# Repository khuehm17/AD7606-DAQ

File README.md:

# AD7606-DAQ

## Hardware
- STM32F103
- ADC Module: AD7606

## Firmware
- C/C++
- STM HAL Driver

### References
- Official AD7606 driver from Analog: https://github.com/analogdevicesinc/no-OS/tree/master/drivers/adc/ad7606
- MrWangShai project: https://github.com/MrWangShuai/stm32-AD7606
- Official AD7606 datasheet: https://www.analog.com/media/en/technical-documentation/data-sheets/ad7606_7606-6_7606-4.pdf
- Official STM32F103 manual: https://www.st.com/resource/en/reference_manual/cd00171190-stm32f101xx-stm32f102xx-stm32f103xx-stm32f105xx-and-stm32f107xx-advanced-arm-based-32-bit-mcus-stmicroelectronics.pdf

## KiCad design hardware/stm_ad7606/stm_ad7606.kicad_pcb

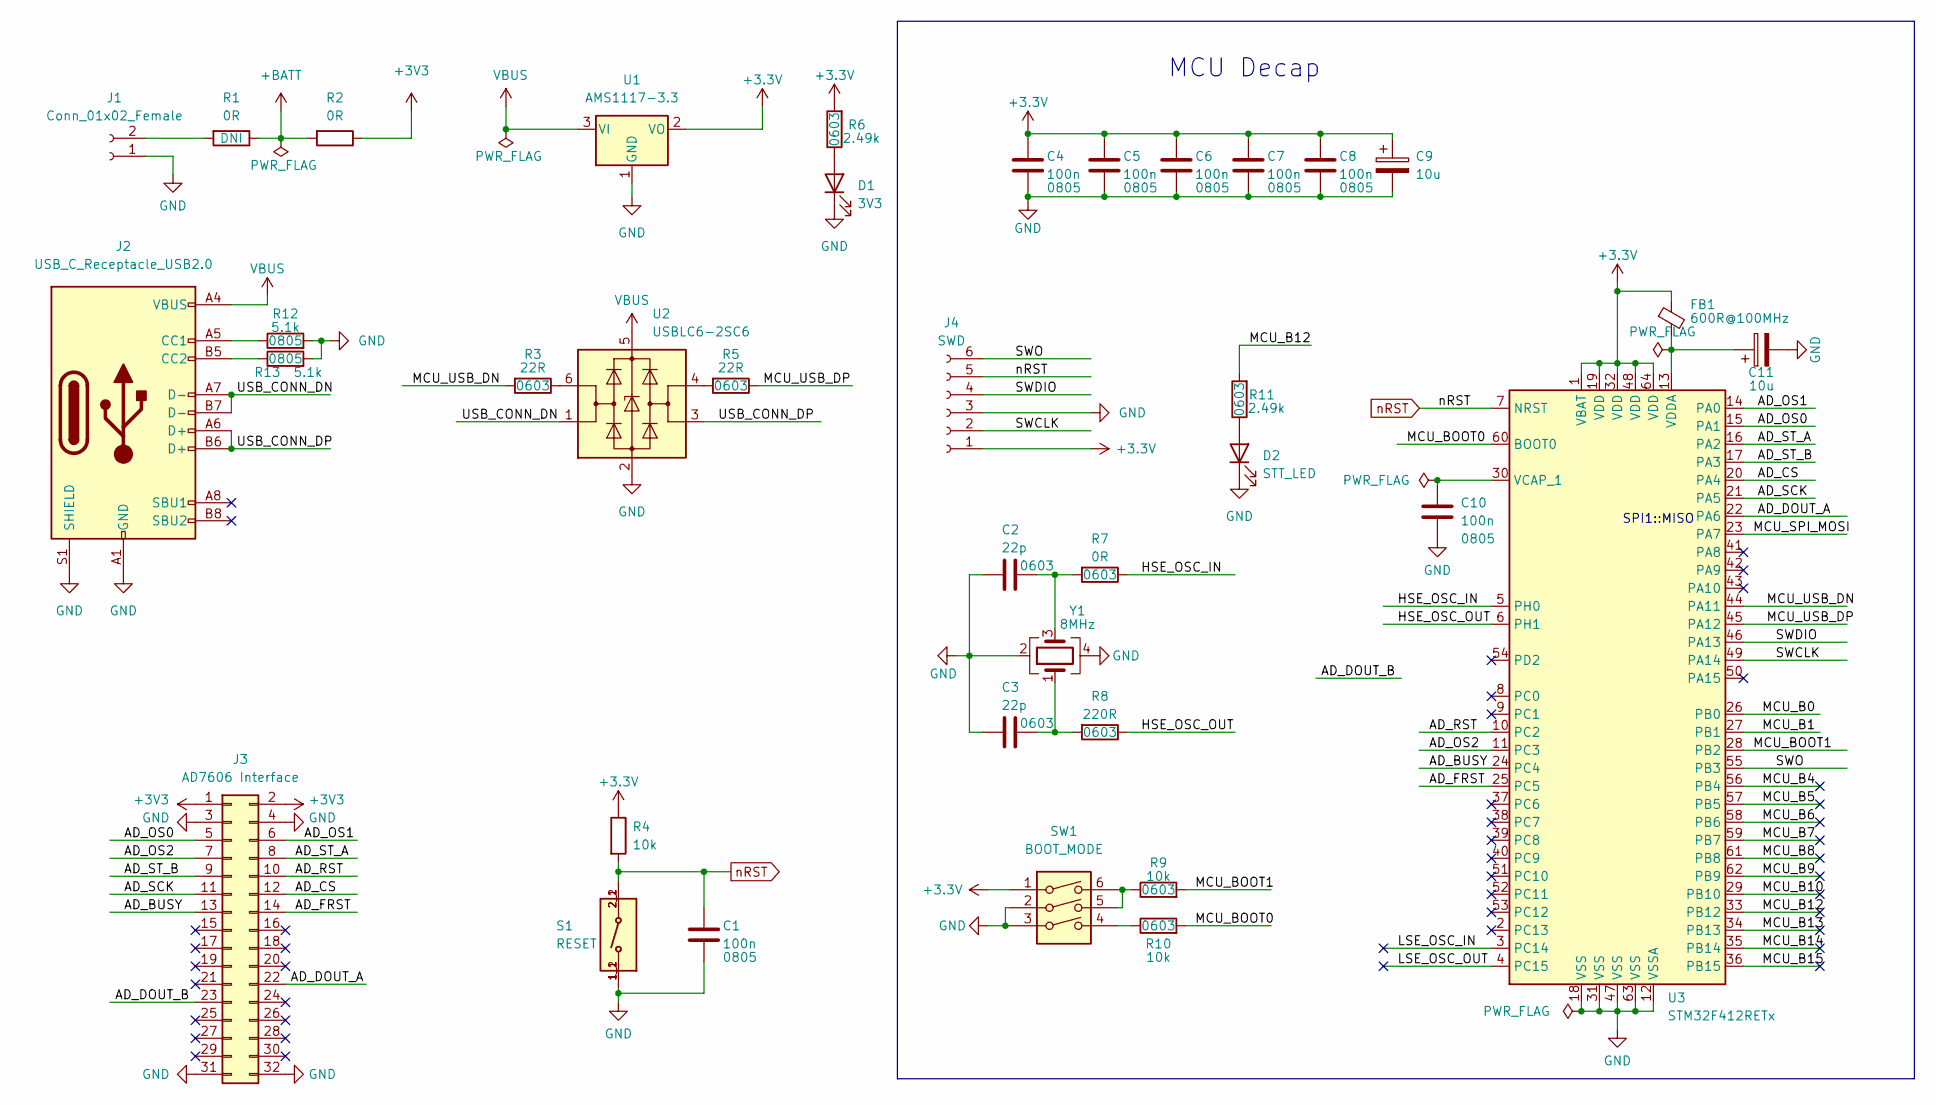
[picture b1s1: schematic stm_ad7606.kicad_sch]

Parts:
C1, C4, C5, C6, C7, C8, C10: 100n; C_0805_2012Metric
C2, C3: 22p; C_0603_1608Metric
C9, C11: 10u; CP_EIA-3216-10_Kemet-I
D1: 3V3; LED_0805_2012Metric
D2: STT_LED; LED_0805_2012Metric
FB1: 600R@100MHz; L_0805_2012Metric
J1: Conn_01x02_Female; JST_PH_B2B-PH-K_1x02_P2.00mm_Vertical
J2: USB_C_Receptacle_USB2.0; USB_C_Receptacle_HRO_TYPE-C-31-M-12
J3: AD7606 Interface; PinHeader_2x16_P2.54mm_Vertical
J4: SWD; PinHeader_1x06_P2.54mm_Vertical
R1, R2, R7: 0R; R_0603_1608Metric
R3, R5: 22R; R_0603_1608Metric
R4: 10k; R_0805_2012Metric
R6, R11: 2.49k; R_0603_1608Metric
R8: 220R; R_0603_1608Metric
R9, R10: 10k; R_0603_1608Metric
R12, R13: 5.1k; R_0805_2012Metric
S1: RESET; SW_KMR621NGLFS; PARTREV N/A
SW1: BOOT_MODE; SW_DIP_SPSTx03_Slide_KingTek_DSHP03TS_W7.62mm_P1.27mm
U1: AMS1117-3.3; SOT-223-3_TabPin2
U2: USBLC6-2SC6; SOT-23-6
U3: STM32F412RETx; LQFP-64_10x10mm_P0.5mm
Y1: 8MHz; Crystal_SMD_5032-4Pin_5.0x3.2mm

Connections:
+BATT: R1.1, R2.2
/AD_BUSY: J3.13, U3.24 (PC4)
/AD_CS: J3.12, U3.20 (PA4)
/AD_DOUT_A: J3.22, U3.22 (PA6)
/AD_DOUT_B: J3.23
/AD_FRST: J3.14, U3.25 (PC5)
/AD_OS0: J3.5, U3.15 (PA1)
/AD_OS1: J3.6, U3.14 (PA0)
/AD_OS2: J3.7, U3.11 (PC3)
/AD_RST: J3.10, U3.10 (PC2)
/AD_SCK: J3.11, U3.21 (PA5)
/AD_ST_A: J3.8, U3.16 (PA2)
/AD_ST_B: J3.9, U3.17 (PA3)
/HSE_OSC_IN: R7.1, U3.5 (PH0)
/HSE_OSC_OUT: R8.1, U3.6 (PH1)
/LSE_OSC_IN: U3.3 (PC14)
/LSE_OSC_OUT: U3.4 (PC15)
/MCU_B0: U3.26 (PB0)
/MCU_B1: U3.27 (PB1)
/MCU_B4: U3.56 (PB4)
/MCU_B5: U3.57 (PB5)
/MCU_B6: U3.58 (PB6)
/MCU_B7: U3.59 (PB7)
/MCU_B8: U3.61 (PB8)
/MCU_B9: U3.62 (PB9)
/MCU_B10: U3.29 (PB10)
/MCU_B12: R11.2, U3.33 (PB12)
/MCU_B13: U3.34 (PB13)
/MCU_B14: U3.35 (PB14)
/MCU_B15: U3.36 (PB15)
/MCU_BOOT0: R10.2, U3.60 (BOOT0)
/MCU_BOOT1: R9.2, U3.28 (PB2)
/MCU_SPI_MOSI: U3.23 (PA7)
/MCU_USB_DN: R3.2, U3.44 (PA11)
/MCU_USB_DP: R5.1, U3.45 (PA12)
/SWCLK: J4.2, U3.49 (PA14)
/SWDIO: J4.4, U3.46 (PA13)
/SWO: J4.6, U3.55 (PB3)
/USB_CONN_DN: J2.A7 (D-), J2.B7 (D-), U2.1 (I/O1)
/USB_CONN_DP: J2.A6 (D+), J2.B6 (D+), U2.3 (I/O2)
GND: C1.2, C2.2, C3.2, C4.2, C5.2, C6.2, C7.2, C8.2, C9.2, C10.2, C11.2, D1.1 (K), D2.1 (K), J1.1, J2.A1 (GND), J2.A12 (GND), J2.B1 (GND), J2.B12 (GND), J2.S1 (SHIELD), J3.3, J3.4, J3.31, J3.32, J4.3, R12.2, R13.2, S1.1_1, S1.1_2, SW1.2, SW1.3, U1.1 (GND), U2.2 (GND), U3.12 (VSSA), U3.18 (VSS), U3.31 (VSS), U3.47 (VSS), U3.63 (VSS), Y1.2, Y1.4
unnamed: C2.1, R7.2, Y1.3
unnamed: C3.1, R8.2, Y1.1
unnamed: C10.1, U3.30 (VCAP_1)
unnamed: C11.1, FB1.2, U3.13 (VDDA)
unnamed: D1.2 (A), R6.1
unnamed: D2.2 (A), R11.1
unnamed: J1.2, R1.2
unnamed: J2.A5 (CC1), R12.1
unnamed: J2.B5 (CC2), R13.1
unnamed: R3.1, U2.6 (I/O1)
unnamed: R5.2, U2.4 (I/O2)
unnamed: R9.1, SW1.5, SW1.6
unnamed: R10.1, SW1.4
VBUS: J2.A4 (VBUS), J2.A9 (VBUS), J2.B4 (VBUS), J2.B9 (VBUS), U1.3 (VI), U2.5 (VBUS)
nRST: C1.1, J4.5, R4.2, S1.2_1, S1.2_2, U3.7 (NRST)

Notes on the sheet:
SPI1::MISO
MCU Decap

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
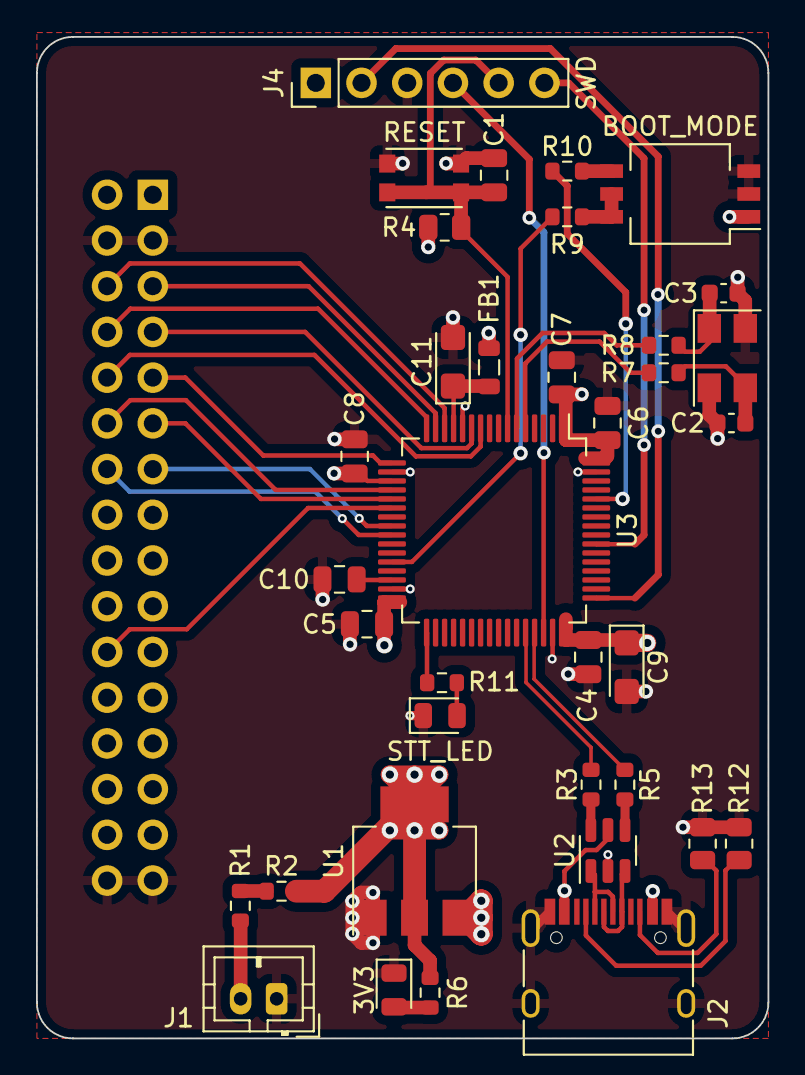
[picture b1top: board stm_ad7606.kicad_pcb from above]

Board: 4 copper layers, 40.6 x 55.6 mm, 37 parts (1 on the bottom side), 41 nets.

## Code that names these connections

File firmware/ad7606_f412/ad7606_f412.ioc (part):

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Mcu.Name=STM32F412R(E-G)Tx
Mcu.Package=LQFP64
Mcu.UserName=STM32F412RETx
PA0.GPIOParameters=GPIO_Label
PA0.GPIO_Label=AD_OS1
PA0.Signal=GPIO_Output
PA1.GPIOParameters=GPIO_Label
PA1.GPIO_Label=AD_0S0
PA1.Signal=GPIO_Output
PA11.GPIOParameters=GPIO_Label
PA11.GPIO_Label=MCU_USB_DN
PA11.Mode=Device_Only
PA11.Signal=USB_OTG_FS_DM
PA12.GPIOParameters=GPIO_Label
PA12.GPIO_Label=MCU_USB_DP
PA12.Mode=Device_Only
PA12.Signal=USB_OTG_FS_DP
PA2.GPIOParameters=GPIO_Label
PA2.GPIO_Label=AD_ST_A
PA2.Signal=S_TIM2_CH3
PA3.GPIOParameters=GPIO_Label
PA3.GPIO_Label=AD_ST_B
PA3.Signal=S_TIM5_CH4
PA4.GPIOParameters=GPIO_Label
PA4.GPIO_Label=AD_CS
PA4.Mode=NSS_Signal_Hard_Input
PA4.Signal=SPI1_NSS
PA5.GPIOParameters=GPIO_Label
PA5.GPIO_Label=AD_SCK
PA5.Mode=Full_Duplex_Master
PA5.Signal=SPI1_SCK
PA6.GPIOParameters=GPIO_Label
PA6.GPIO_Label=AD_DOU_A
PA6.Mode=Full_Duplex_Master
PA6.Signal=SPI1_MISO
PA7.Mode=Full_Duplex_Master
PA7.Signal=SPI1_MOSI
PC2.GPIOParameters=GPIO_Label
PC2.GPIO_Label=AD_RST
PC2.Signal=GPIO_Output
PC3.GPIOParameters=GPIO_Label
PC3.GPIO_Label=AD_OS2
PC3.Signal=GPIO_Output
PC4.GPIOParameters=GPIO_Label
PC4.GPIO_Label=AD_BUSY
PC4.Signal=GPIO_Input
PC5.GPIOParameters=GPIO_Label
PC5.GPIO_Label=AD_FRST
PC5.Signal=GPIO_Input
PH0\ -\ OSC_IN.Mode=HSE-External-Oscillator
PH0\ -\ OSC_IN.Signal=RCC_OSC_IN
PH1\ -\ OSC_OUT.Mode=HSE-External-Oscillator
PH1\ -\ OSC_OUT.Signal=RCC_OSC_OUT
board=custom

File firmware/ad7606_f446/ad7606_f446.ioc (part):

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Mcu.Name=STM32F446R(C-E)Tx
Mcu.Package=LQFP64
Mcu.UserName=STM32F446RETx
PA0-WKUP.GPIOParameters=GPIO_Speed,PinState,GPIO_PuPd,GPIO_Label
PA0-WKUP.GPIO_Label=AD_OS1
PA0-WKUP.GPIO_PuPd=GPIO_NOPULL
PA0-WKUP.GPIO_Speed=GPIO_SPEED_FREQ_LOW
PA0-WKUP.PinState=GPIO_PIN_RESET
PA0-WKUP.Signal=GPIO_Output
PA1.GPIOParameters=GPIO_Speed,PinState,GPIO_Label
PA1.GPIO_Label=AD_OS0
PA1.GPIO_Speed=GPIO_SPEED_FREQ_LOW
PA1.PinState=GPIO_PIN_RESET
PA1.Signal=GPIO_Output
PA11.Mode=Device_Only
PA11.Signal=USB_OTG_FS_DM
PA12.Mode=Device_Only
PA12.Signal=USB_OTG_FS_DP
PA2.Mode=Asynchronous
PA2.Signal=USART2_TX
PA3.Mode=Asynchronous
PA3.Signal=USART2_RX
PA4.GPIOParameters=GPIO_Speed,GPIO_Label
PA4.GPIO_Label=AD_CS
PA4.GPIO_Speed=GPIO_SPEED_FREQ_MEDIUM
PA4.Mode=NSS_Signal_Hard_Output
PA4.Signal=SPI1_NSS
PA5.GPIOParameters=GPIO_Speed,GPIO_Label
PA5.GPIO_Label=AD_SCK
PA5.GPIO_Speed=GPIO_SPEED_FREQ_MEDIUM
PA5.Mode=Full_Duplex_Master
PA5.Signal=SPI1_SCK
PA6.GPIOParameters=GPIO_Speed,GPIO_Label
PA6.GPIO_Label=AD_DOU_A
PA6.GPIO_Speed=GPIO_SPEED_FREQ_MEDIUM
PA6.Mode=Full_Duplex_Master
PA6.Signal=SPI1_MISO
PA7.Mode=Full_Duplex_Master
PA7.Signal=SPI1_MOSI
PB3.GPIOParameters=GPIO_Speed,GPIO_PuPd,GPIO_Label
PB3.GPIO_Label=AD_CO_A
PB3.GPIO_PuPd=GPIO_NOPULL
PB3.GPIO_Speed=GPIO_SPEED_FREQ_MEDIUM
PB3.Signal=S_TIM2_CH2
PC2.GPIOParameters=GPIO_Speed,PinState,GPIO_Label
PC2.GPIO_Label=AD_RST
PC2.GPIO_Speed=GPIO_SPEED_FREQ_LOW
PC2.PinState=GPIO_PIN_RESET
PC2.Signal=GPIO_Output
PC3.GPIOParameters=GPIO_Speed,PinState,GPIO_Label
PC3.GPIO_Label=AD_OS2
PC3.GPIO_Speed=GPIO_SPEED_FREQ_LOW
PC3.PinState=GPIO_PIN_RESET
PC3.Signal=GPIO_Output
PC4.GPIOParameters=GPIO_Label
PC4.GPIO_Label=AD_BUSY
PC4.Signal=GPIO_Input
PC5.GPIOParameters=GPIO_Label
PC5.GPIO_Label=AD_FRST
PC5.Signal=GPIO_Input
PH0-OSC_IN.Mode=HSE-External-Oscillator
PH0-OSC_IN.Signal=RCC_OSC_IN
PH1-OSC_OUT.Mode=HSE-External-Oscillator
PH1-OSC_OUT.Signal=RCC_OSC_OUT
RCC.HSE_VALUE=8000000
RCC.SYSCLKFreq_VALUE=84000000
RCC.SYSCLKSource=RCC_SYSCLKSOURCE_PLLCLK
board=custom

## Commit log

2022-05-08 init gitignore
2022-05-08 init firmware project
2022-05-09 add ad7606 useful resources
2022-05-09 add and test blink led demo STM32f103 with platformio
2022-05-22 chore: update gitignore file
2022-06-12 feat[hardware]: add PCB hardware design Kicad6
2022-06-12 docs: stm32f103, ad7606 datasheet
2022-06-18 doc: update docs on issue #1
2022-06-21 Update study_docs_#1.md
    docs: update SPI protocol on issue #1
2022-06-21 Update study_docs_#1.md
    Docs: SPI Protocol on Issue #1
2022-06-22 Updates study_docs_#1.md
    Notes on SPI pins and simultaneous sampling mode of ad7606
2022-06-27 feat[sw]: init hw configuration for project
2022-06-27 feat[hw]: add interface connection MCU vs 7606
2022-06-30 docs: update system diagram and connection diagram (issue #2)
2022-07-01 Code Generation (Issue #3 )
    Code generated according to System architecture, STM32CubeIDE used as development tool
2022-07-06 SPI Implementation (Issue #3 )
    Updates on .ioc file following HAL_SPI Procedures
    Add and test SPI Communication Demo
2022-07-11 AD7606 IO Pins Configuration (Issue #4 )
    AD_OS[2:0], AD_RST and AD_BUSY Pins Configuration Completed
2022-07-13 AD7606 IO Pins Configurations (#4)
    Complete implementation for required pins
2022-07-16 Code Update (#4)
2022-07-17 Firmware Update (#4)
    Test Code updates for stm32f446re
2022-07-20 Firmware Updates (#4)
2022-07-21 docs: add system clk config img for stmf412
2022-07-31 Firmware Updates ( #4 )
2022-08-07 feat[sw]: init USB middleware for project (issue #5)
2022-08-14 feat[sw]: init uart for transmitting data from board to PC
2022-08-14 chore[sw]: auto-generated by ide
2022-08-15 chore[sw]: modify adc transfer function
2022-08-16 chore[sw]: spi interface modification
2022-08-16 chore[sw]: modify spi interface
2022-08-17 feat[sw]: add stm32f407 firmware directory
    Features:
    - ADC interface with Non-DMA SPI
    - USB interface FS VCP
    - TIMER PWM 1kHz
2022-08-19 feat[sw]: add ad7606 device driver (Issue #6 )
    Features:
    - ad7606 handle structure
    - ad7606 oversampling ratio structure definition
    - ad7606 adc channel structure ratio
    - Necessary macros
    - Necessary functions
2022-09-28 chore[sw]: debug program
